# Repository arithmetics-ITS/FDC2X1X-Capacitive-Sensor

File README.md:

# Breakout Board: FDC2212 EMI-Resistant 28-Bit Capacitance-to-Digital Converter for Proximity and  Level Sensing Application
## Description

Capacitive sensing is a low-power, low-cost, high-resolution contactless sensing technique that can be applied to a variety of applications ranging from proximity detection and gesture recognition to remote liquid level sensing. The sensor in a capacitive sensing system is any metal or conductor, allowing for low cost and highly flexible system design. The main challenge limiting sensitivity in capacitive sensing applications is noise susceptibility of the sensors. With the FDC2x1x innovative EMI resistant
architecture, performance can be maintained even in presence of high-noise environments.

The FDC2x1x is a multi-channel family of noise-and EMI-resistant, high-resolution, high-speed capacitance-to-digital converters for  implementing capacitive sensing solutions. The devices employ an innovative narrow-band based architecture to offer high rejection of noise and interferers while providing high resolution at highspeed. The devices support a wide excitation frequency range, offering flexibility in system design. A wide frequency range is especially useful for reliable sensing of conductive liquids such as detergent, soap, and ink.

## Features

- Texas Instruments FDC2212
- CTS Model 625 - 40MHz ultra-low voltage clock oscillator
-  SiP3243 - Ultra Low Leakage Load Switch

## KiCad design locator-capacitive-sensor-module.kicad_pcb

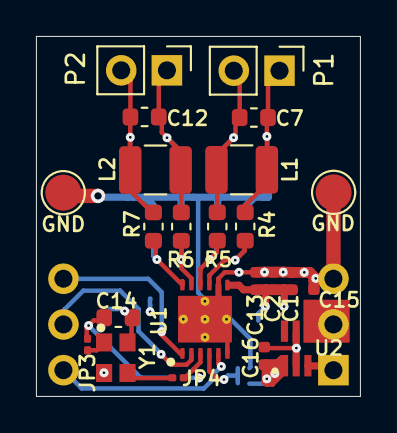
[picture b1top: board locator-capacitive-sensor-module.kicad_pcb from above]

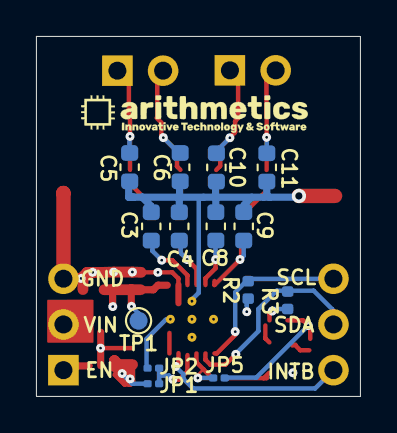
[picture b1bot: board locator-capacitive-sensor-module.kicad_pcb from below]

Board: 4 copper layers, 18.0 x 20.0 mm, 39 parts (15 on the bottom side), 19 nets.

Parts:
C1, C15: 1uF; C_0402_1005Metric
C2, C16: 0.1uF; C_0402_1005Metric
C3, C4, C5, C6, C8, C9, C10, C11: 18pF; C_0603_1608Metric
C7, C12: 33pF; C_0603_1608Metric
C13: 0.01uF; C_0402_1005Metric
C14: 0.01uF; C_0603_1608Metric
ICO1: arithmetics_logo_2400DPI; logo_2400_DPI
J1: FDC2112_Module_DIP; Capacitive_Sensor_Module_Footprint_2
JP1, JP2, JP3, JP4, JP5: 0R; R_0201_0603Metric
L1, L2: 18uH; L_1210_3225Metric
P1: Sensor 1; PinHeader_1x02_P2.54mm_Vertical
P2: Sensor 2; PinHeader_1x02_P2.54mm_Vertical
R2, R3: 10k; R_0402_1005Metric
R4, R5, R6, R7: 0R; R_0603_1608Metric
TP1: GND; TestPoint_Pad_D1.0mm
TP2, TP4: GND; TestPoint_Pad_D2.0mm
U1: FDC2212DNTT; FDC2112-Q1
U2: SIP32432DR3
Y1: Val**; 625L3C040M00000

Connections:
+3V3: C15.1, J1.2, U2.4
/ADDR: JP1.2, JP2.1, U1.4
/CLKIN: JP4.2, JP5.1, U1.3
/EN: J1.1, U2.3
/IN0A: C3.1, R4.2, U1.9
/IN0B: C4.2, R5.2, U1.10
/IN1A: C8.1, R6.2, U1.11
/IN1B: C9.2, R7.2, U1.12
/INTB: J1.6, U1.5
/SCL: J1.4, R2.2, U1.1
/SDA: J1.5, R3.2, U1.2
/Sensing_Network_1/OUT1: C5.1, C7.1, L1.2, P1.1, R4.1
/Sensing_Network_1/OUT2: C6.2, C7.2, L1.1, P1.2, R5.1
/Sensing_Network_2/OUT1: C10.1, C12.1, L2.2, P2.1, R6.1
/Sensing_Network_2/OUT2: C11.2, C12.2, L2.1, P2.2, R7.1
/VCC: C1.1, C2.1, C13.1, C14.1, C16.1, JP1.1, R2.1, R3.1, TP1.1, U1.7, U2.1, Y1.4
GND: C1.2, C2.2, C3.2, C4.1, C5.2, C6.1, C8.2, C9.1, C10.2, C11.1, C13.2, C14.2, C15.2, C16.2, J1.3, JP2.2, JP3.2, JP5.2, TP2.1, TP4.1, U1.6, U1.8, U1.13, U2.2, U2.5, Y1.2
unnamed: JP3.1, Y1.1
unnamed: JP4.1, Y1.3

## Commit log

2021-02-22 Initial
